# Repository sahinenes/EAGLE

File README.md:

## EAGLE 
# EAGLE YAZI KOMUTLARI 

group all;            # Her şeyi grupla
    
smash (C>0 0);       # Gruptaki her şeyi parçala
    
display none tNames bNames tval bval; #İSTEĞE BAĞLI: değişiklikleri sınırla
     isimler ve değerler
    
group all;             # Parçalanmış metinler dahil her şeyi gruplayın.
    
change font vector (C>0 0); # Yazı tipini vektör yazı tipine değiştirin
    
change size 50mil (C>0 0); # Yazı tipi boyutunu değiştirin
    
change ratio 15 (C>0 0); # Genişlik: yükseklik oranını değiştirin

display last; #Son halini göster

# LEZZETLİ ROBOT TARİFLERİ EAGLE BAŞLANGIÇ YAYINLARI

* https://www.youtube.com/watch?v=clBWAKnVNWI  # Sıfırdan EAGLE ile PCB tasarım yayınları başlıyor - ( Bölüm 0 )
* https://www.youtube.com/watch?v=m92im1b6kVI  # Eagle Ne ile Başlayıp, Sıfırdan Kart Çizip, Üretime Göndereceğiz! ( PART 1 / 2)
* https://www.youtube.com/watch?v=JgwcVjCoXeo  # Eagle Ne ile Başlayıp, Sıfırdan Kart Çizip, Üretime Göndereceğiz! ( PART 2 / 2)

# KAYNAKLAR 
* https://www.arduino.cc/en/uploads/Main/arduino_mini_schematic05.pdf # Arduino Mini Şematik 
* https://store.arduino.cc/usa/arduino-mini-05 # Arduino Mini EAGLE dosyaları bu linkten indirilebilir.

* https://www.researchgate.net/figure/L298N-Motor-Drive-Schematic_fig2_275414953 # L298N Şematik
* http://pdf.datasheetcatalog.com/datasheet/SGSThomsonMicroelectronics/mXxwur.pdf # L298N DataSheet
* https://www.ti.com/lit/ds/symlink/l293.pdf # L293D DataSheet

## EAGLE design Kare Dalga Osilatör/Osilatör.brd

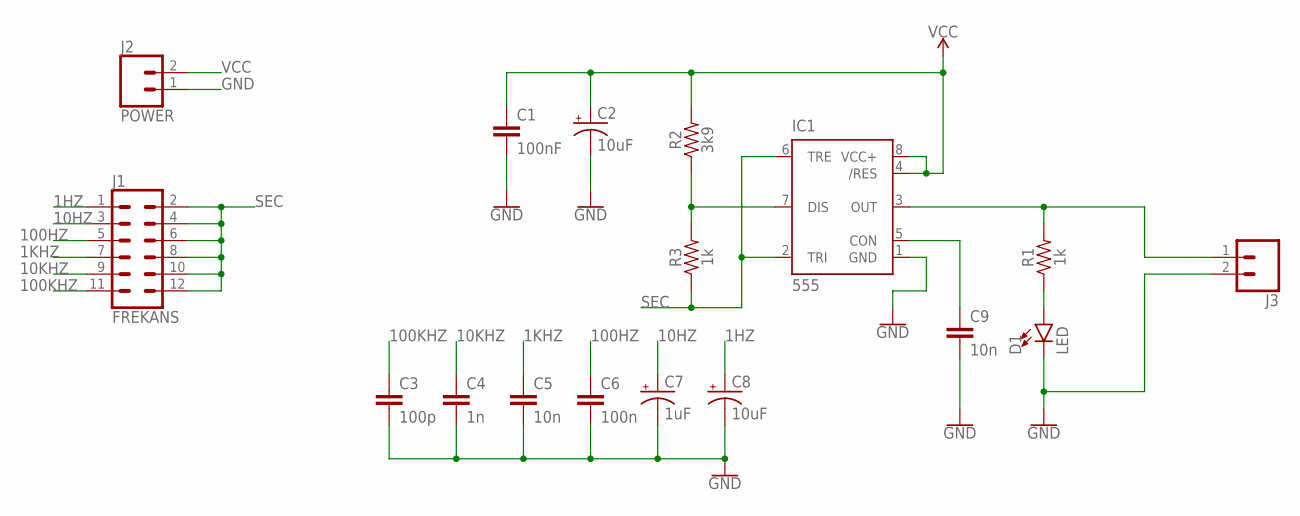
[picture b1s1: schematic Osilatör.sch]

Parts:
C1: 100nF; C2.5-3
C2, C8: 10uF; CPOL-RADIAL-2.5MM-6.5MM
C3: 100p; C2.5-3
C4: 1n; C2.5-3
C5, C9: 10n; C2.5-3
C6: 100n; C2.5-3
C7: 1uF; CPOL-RADIAL-2.5MM-6.5MM
D1: LED; LED_3MM-NS
IC1: 555; DIP08-KIT
J1: FREKANS; 2X6
J2: POWER; 1X02
J3: CONN_02; 1X02
R1, R3: 1k; AXIAL-0.3
R2: 3k9; AXIAL-0.3

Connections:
1HZ: C8.1 (+), J1.1
1KHZ: C5.1, J1.7
10HZ: C7.1 (+), J1.3
10KHZ: C4.1, J1.9
100HZ: C6.1, J1.5
100KHZ: C3.1, J1.11
GND: C1.2, C2.2 (-), C3.2, C4.2, C5.2, C6.2, C7.2 (-), C8.2 (-), C9.2, D1.K (C), IC1.1 (GND), J2.1, J3.2
unnamed: IC1.3 (OUT), J3.1, R1.P$2 (2)
unnamed: D1.A, R1.P$1 (1)
unnamed: C9.1, IC1.5 (CON)
unnamed: IC1.7 (DIS), R2.P$1 (1), R3.P$2 (2)
SEC: IC1.2 (TRI), IC1.6 (TRE), J1.2, J1.4, J1.6, J1.8, J1.10, J1.12, R3.P$1 (1)
VCC: C1.1, C2.1 (+), IC1.4 (/RES), IC1.8 (VCC+), J2.2, R2.P$2 (2)

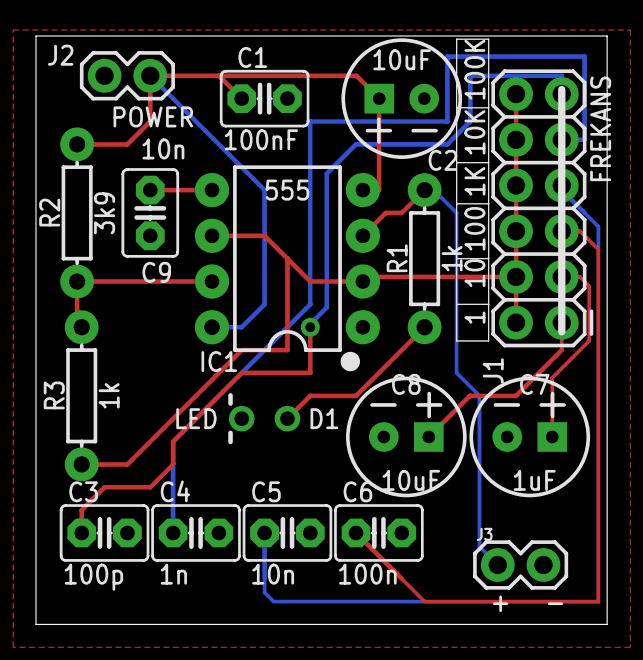
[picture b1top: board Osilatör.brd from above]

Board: 2 copper layers, 31.7 x 32.7 mm, 17 parts (0 on the bottom side), 13 nets.

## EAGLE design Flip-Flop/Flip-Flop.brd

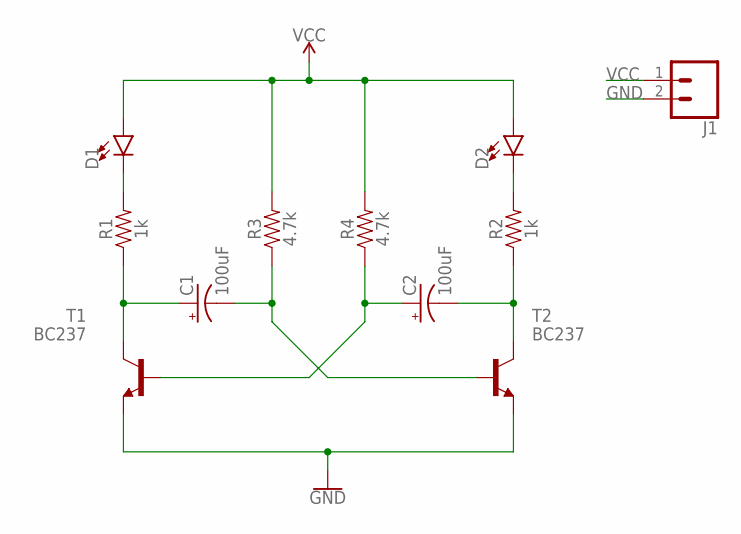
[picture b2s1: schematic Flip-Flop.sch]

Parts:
C1, C2: 100uF; CPOL-RADIAL-2.5MM-6.5MM
D1, D2: LED-3MM-NO_SILK; LED_3MM-NS
J1: CONN_02; 1X02
R1, R2: 1k; AXIAL-0.3
R3, R4: 4.7k; AXIAL-0.3
T1, T2: BC237; TO92

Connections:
GND: J1.2, T1.1 (E), T2.1 (E)
unnamed: D1.K (C), R1.P$2 (2)
unnamed: C1.1 (+), R1.P$1 (1), T1.3 (C)
unnamed: D2.K (C), R2.P$2 (2)
unnamed: C1.2 (-), R3.P$1 (1), T2.2 (B)
unnamed: C2.1 (+), R4.P$1 (1), T1.2 (B)
unnamed: C2.2 (-), R2.P$1 (1), T2.3 (C)
VCC: D1.A, D2.A, J1.1, R3.P$2 (2), R4.P$2 (2)

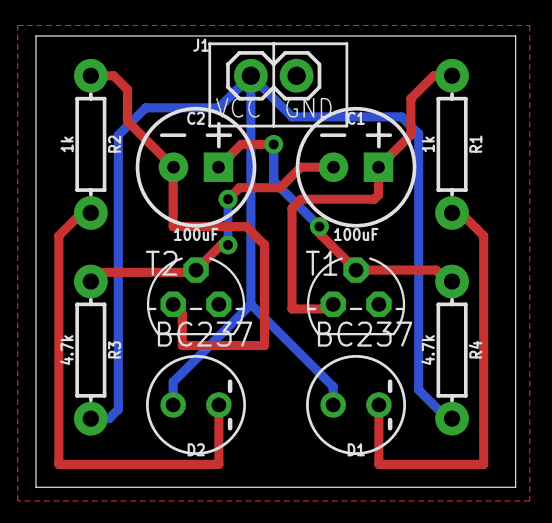
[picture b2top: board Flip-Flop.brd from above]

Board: 2 copper layers, 26.6 x 25.1 mm, 11 parts (0 on the bottom side), 8 nets.

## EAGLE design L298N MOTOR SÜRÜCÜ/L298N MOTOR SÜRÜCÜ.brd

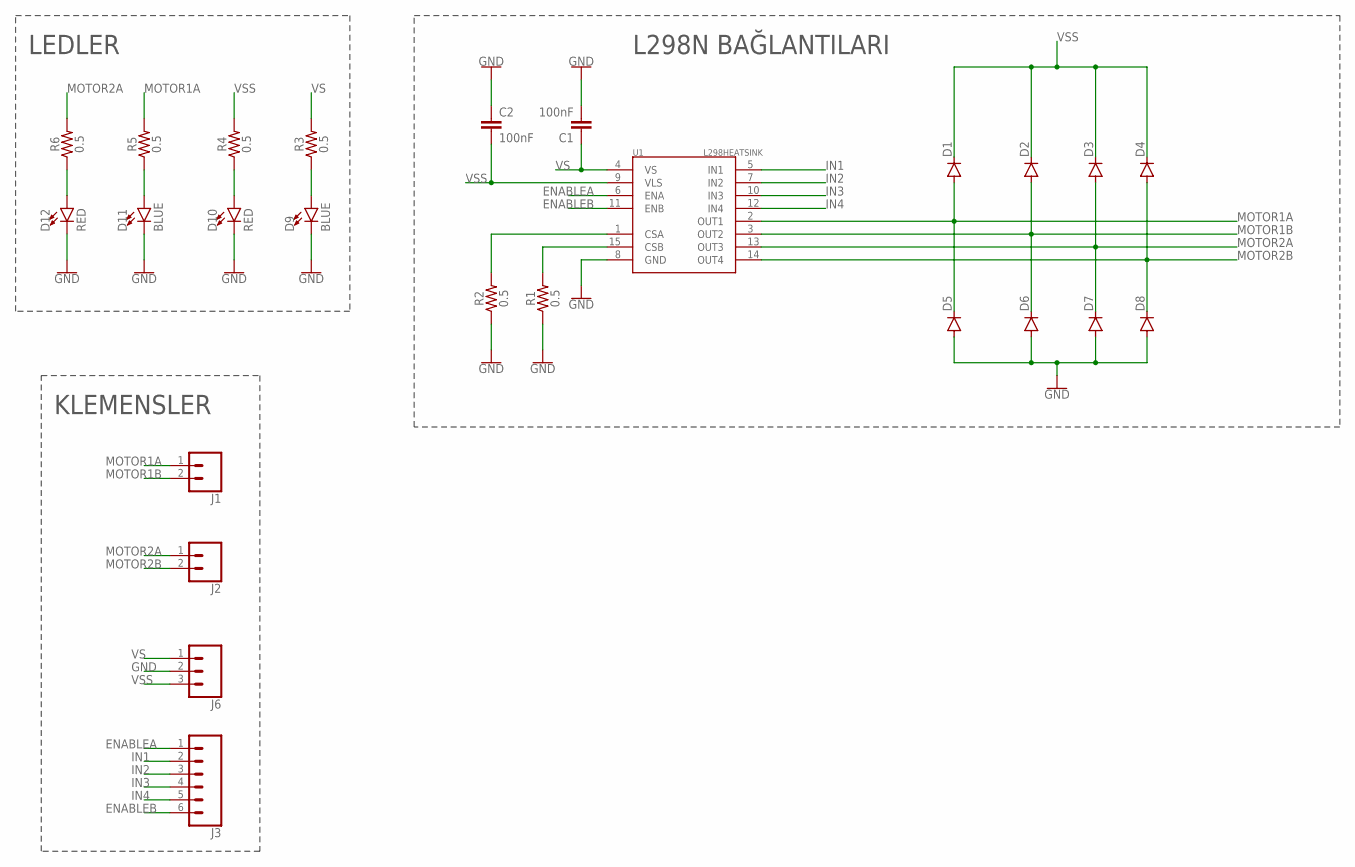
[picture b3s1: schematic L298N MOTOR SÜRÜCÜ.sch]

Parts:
C1, C2: 100nF; 0603
D1, D2, D3, D4, D5, D6, D7, D8: CGRM4007-G; SOD-123_MINI-SMA
D9, D11: BLUE; LED-0603
D10, D12: RED; LED-0603
J1, J2: CONN_02; 1X02
J3: CONN_06SILK_FEMALE_PTH; 1X06
J6: CONN_03; 1X03
R1, R2, R3, R4, R5, R6: 0.5; 0603
U1: L298HEATSINK; MULTIWATT15_6400BGHEATSINK

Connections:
ENABLEA: J3.1, U1.6 (ENA)
ENABLEB: J3.6, U1.11 (ENB)
GND: C1.2, C2.1, D5.A, D6.A, D7.A, D8.A, D9.C, D10.C, D11.C, D12.C, J6.2, R1.1, R2.1, U1.8 (GND)
IN1: J3.2, U1.5 (IN1)
IN2: J3.3, U1.7 (IN2)
IN3: J3.4, U1.10 (IN3)
IN4: J3.5, U1.12 (IN4)
MOTOR1A: D1.A, D5.C, J1.1, R5.2, U1.2 (OUT1)
MOTOR1B: D2.A, D6.C, J1.2, U1.3 (OUT2)
MOTOR2A: D3.A, D7.C, J2.1, R6.2, U1.13 (OUT3)
MOTOR2B: D4.A, D8.C, J2.2, U1.14 (OUT4)
unnamed: R1.2, U1.15 (CSB)
unnamed: R2.2, U1.1 (CSA)
unnamed: D10.A, R4.1
unnamed: D9.A, R3.1
unnamed: D12.A, R6.1
unnamed: D11.A, R5.1
VS: C1.1, J6.1, R3.2, U1.4 (VS)
VSS: C2.2, D1.C, D2.C, D3.C, D4.C, J6.3, R4.2, U1.9 (VLS)

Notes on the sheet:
KLEMENSLER
LEDLER
L298N BAĞLANTILARI

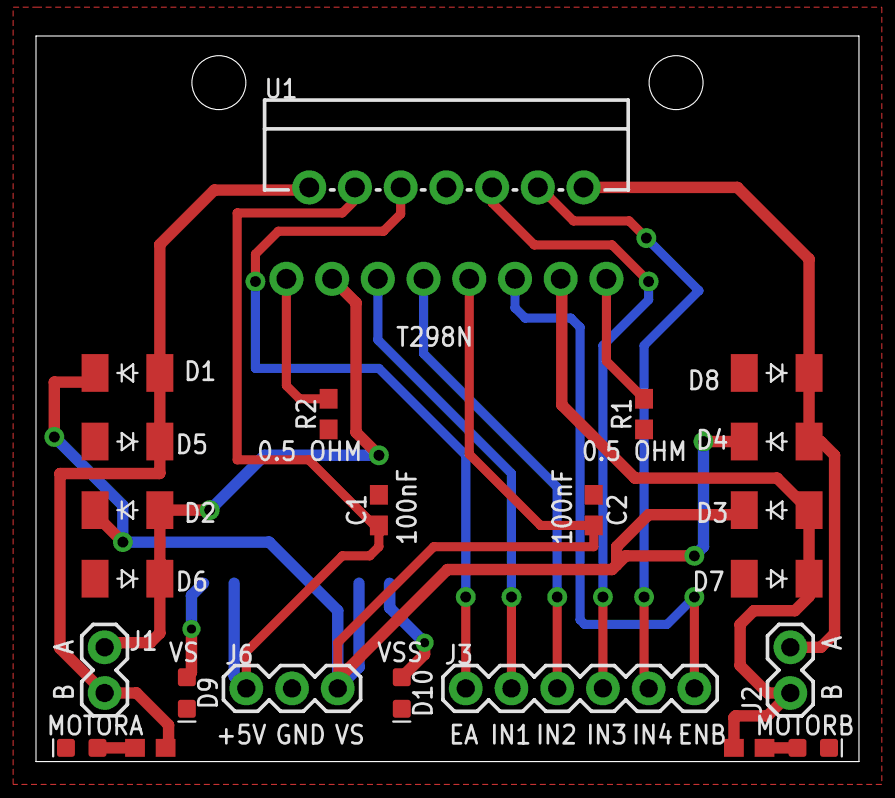
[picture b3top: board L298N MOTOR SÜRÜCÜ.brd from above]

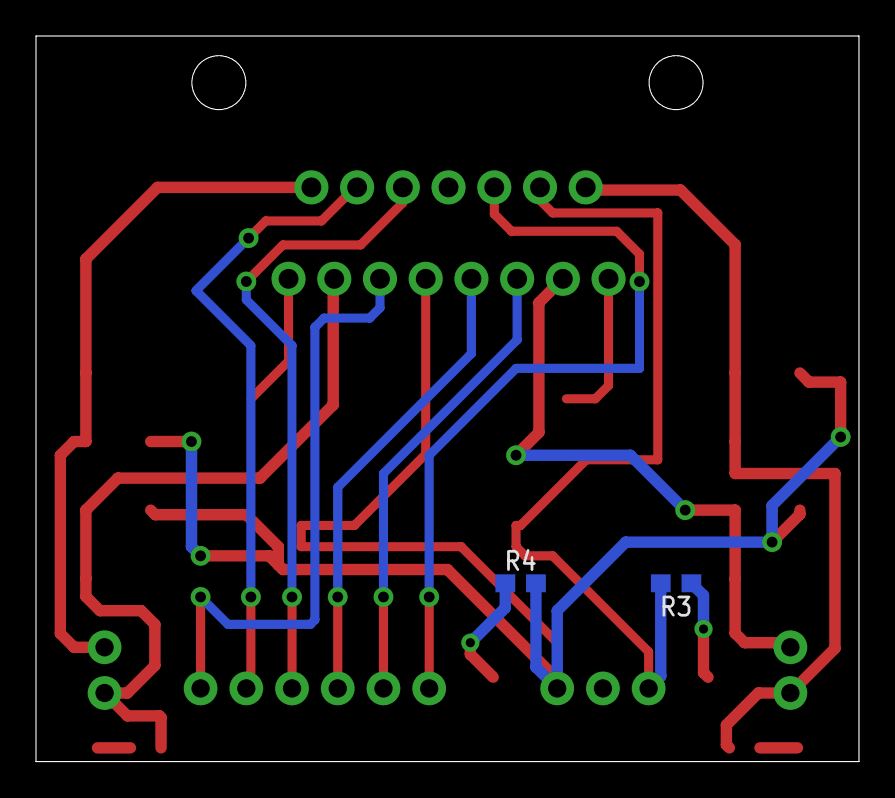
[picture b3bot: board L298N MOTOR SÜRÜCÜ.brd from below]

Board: 2 copper layers, 45.7 x 40.3 mm, 25 parts (2 on the bottom side), 19 nets.

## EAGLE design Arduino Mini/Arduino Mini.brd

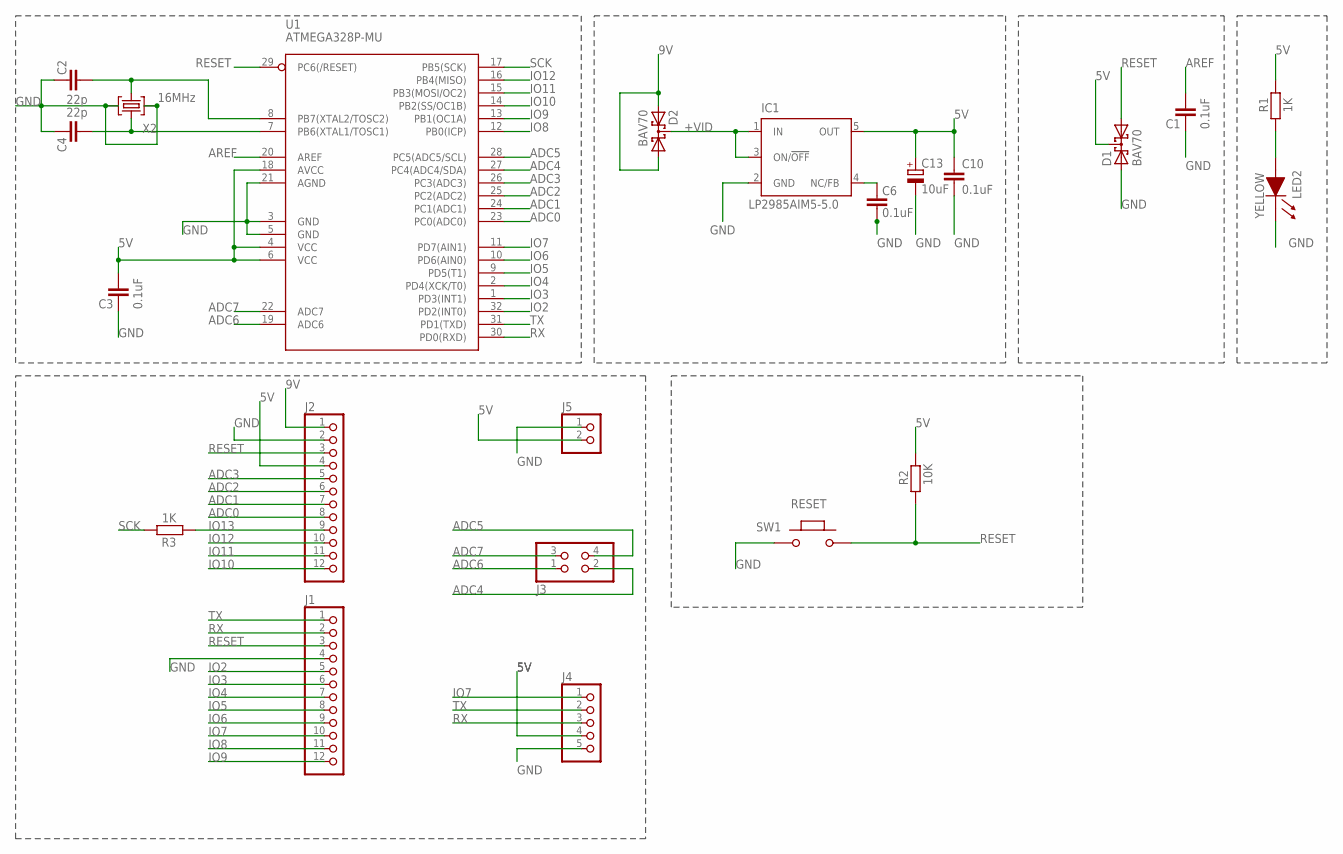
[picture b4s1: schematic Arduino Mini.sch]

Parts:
C1, C3, C6, C10: 0.1uF; C0603-ROUND
C2, C4: 22p; C0603-ROUND
C13: 10uF; SMC_B
D1, D2: BAV70; SOT23
IC1: LP2985AIM5-5.0; SOT23-DBV
J1, J2: PINHD-1X12; 1X12
J3: PINHD-2X2; 2X02
J4: PINHD-1X5; 1X5
J5: PINHD-1X2; 1X2
LED2: YELLOW; SMD_LED0805
R1, R3: 1K; R0603-ROUND
R2: 10K; R0603-ROUND
SW1: RESET; SMD_157SW
U1: ATMEGA328P-MU; MLF32-M1-A
X2: 16MHz; CRYSTAL-3.2-2.5

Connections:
5V: C3.1, C10.1, C13.+, D1.3 (C), IC1.5 (OUT), J2.4, J4.4, J5.2, R1.2, R2.2, U1.4 (VCC), U1.6 (VCC), U1.18 (AVCC)
9V: D2.1 (A1), D2.2 (A2), J2.1
+VID: D2.3 (C), IC1.1 (IN), IC1.3 (ON/!OFF)
ADC0: J2.8, U1.23 (PC0(ADC0))
ADC1: J2.7, U1.24 (PC1(ADC1))
ADC2: J2.6, U1.25 (PC2(ADC2))
ADC3: J2.5, U1.26 (PC3(ADC3))
ADC4: J3.2, U1.27 (PC4(ADC4/SDA))
ADC5: J3.4, U1.28 (PC5(ADC5/SCL))
ADC6: J3.1, U1.19 (ADC6)
ADC7: J3.3, U1.22 (ADC7)
AREF: C1.1, U1.20 (AREF)
GND: C1.2, C2.2, C3.2, C4.2, C6.1, C10.2, C13.-, D1.1 (A1), IC1.2 (GND), J1.4, J2.2, J4.5, J5.1, LED2.1 (CA), SW1.1, U1.3 (GND), U1.5 (GND), U1.21 (AGND), X2.2 (GND), X2.4 (GND)
IO2: J1.5, U1.32 (PD2(INT0))
IO3: J1.6, U1.1 (PD3(INT1))
IO4: J1.7, U1.2 (PD4(XCK/T0))
IO5: J1.8, U1.9 (PD5(T1))
IO6: J1.9, U1.10 (PD6(AIN0))
IO7: J1.10, J4.1, U1.11 (PD7(AIN1))
IO8: J1.11, U1.12 (PB0(ICP))
IO9: J1.12, U1.13 (PB1(OC1A))
IO10: J2.12, U1.14 (PB2(SS/OC1B))
IO11: J2.11, U1.15 (PB3(MOSI/OC2))
IO12: J2.10, U1.16 (PB4(MISO))
IO13: J2.9, R3.1
unnamed: C2.1, U1.8 (PB7(XTAL2/TOSC2)), X2.3 (C2)
unnamed: C6.2, IC1.4 (NC/FB)
unnamed: C4.1, U1.7 (PB6(XTAL1/TOSC1)), X2.1 (C1)
RESET: D1.2 (A2), J1.3, J2.3, R2.1, SW1.2, U1.29 (PC6(/RESET))
RESET1: LED2.2 (AN), R1.1
RX: J1.2, J4.3, U1.30 (PD0(RXD))
SCK: R3.2, U1.17 (PB5(SCK))
TX: J1.1, J4.2, U1.31 (PD1(TXD))

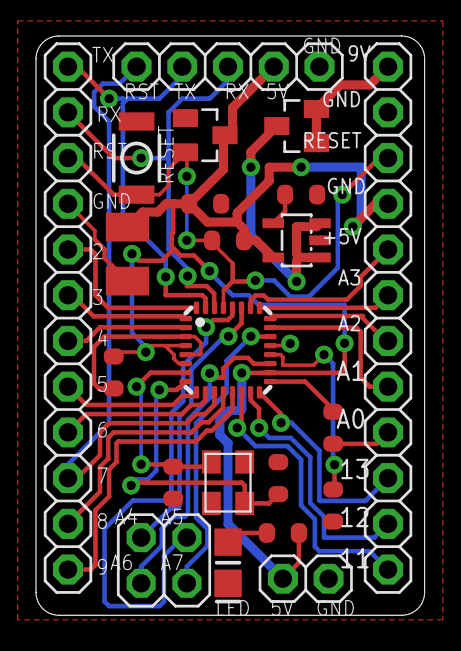
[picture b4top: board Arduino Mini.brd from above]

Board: 2 copper layers, 21.6 x 32.2 mm, 22 parts (0 on the bottom side), 33 nets.

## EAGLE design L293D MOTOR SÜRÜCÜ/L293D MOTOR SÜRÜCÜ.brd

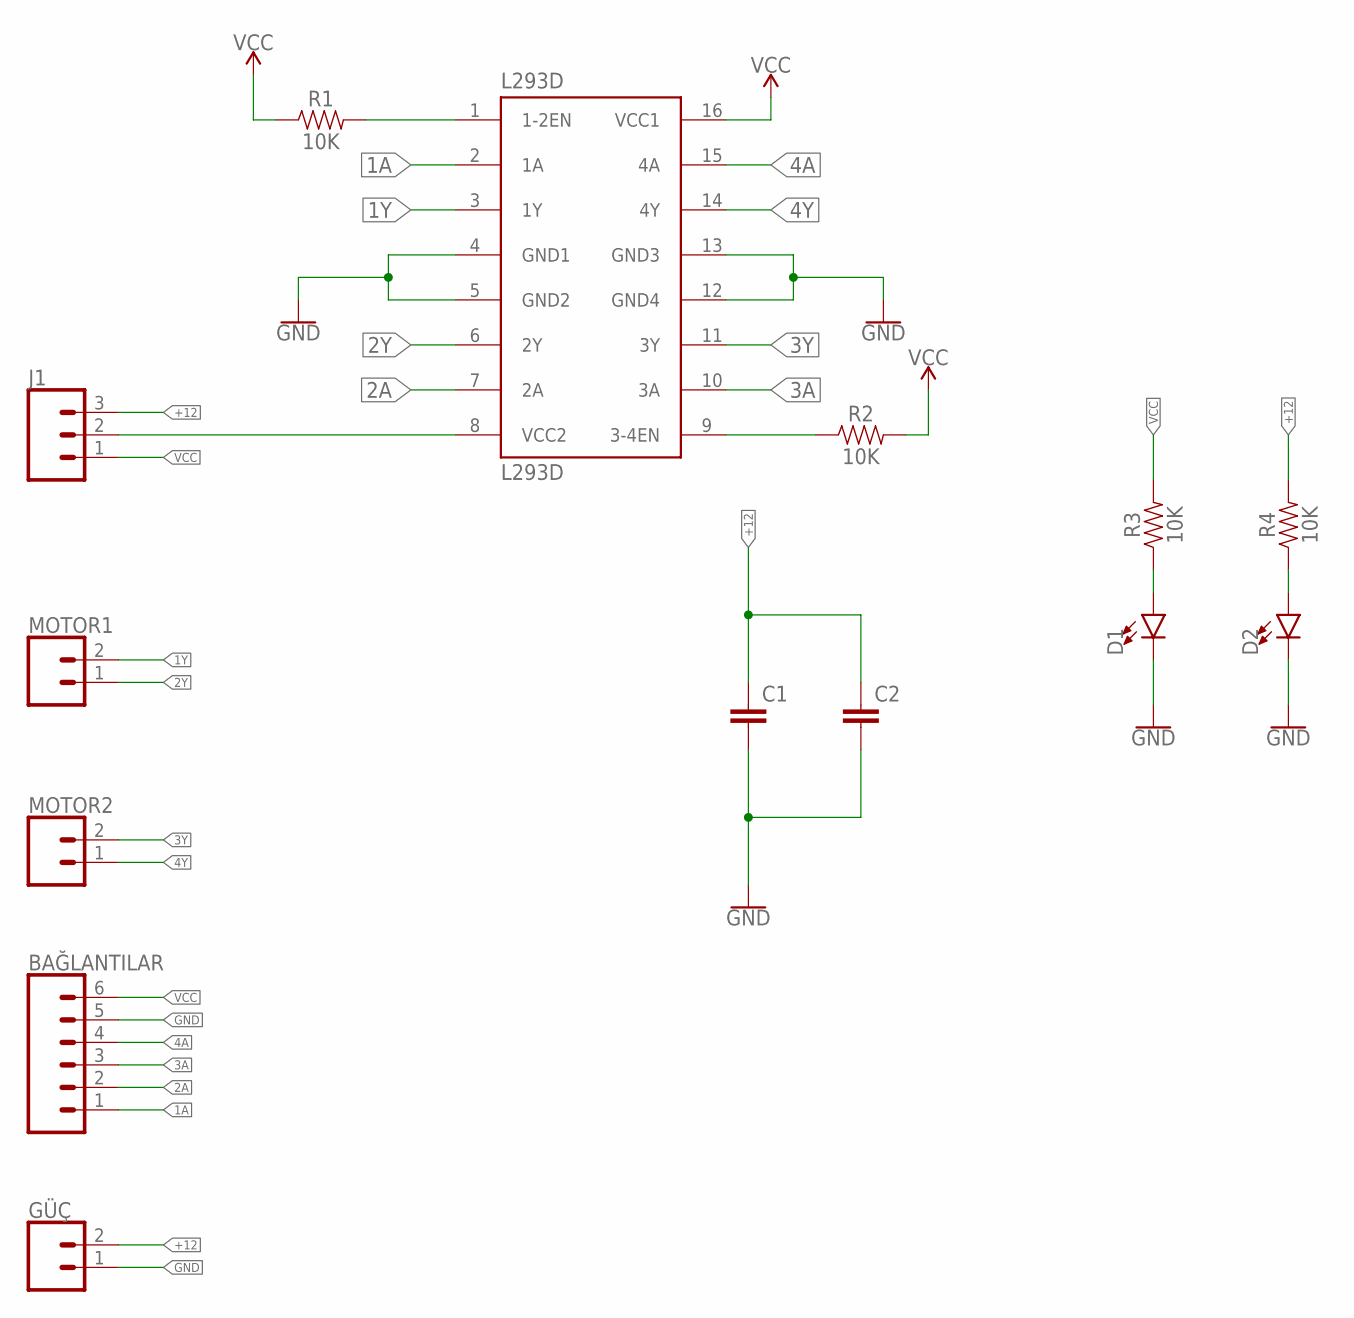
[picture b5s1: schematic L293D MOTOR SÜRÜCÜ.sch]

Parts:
BAĞLANTILAR: CONN_06LOCK; 1X06_LOCK
C1, C2: C2,5-3; C2.5-3
D1, D2: LED-3MM-NO_SILK; LED_3MM-NS
GÜÇ: CONN_02; 1X02
J1: CONN_03; 1X03
L293D: L293D; DIL16
MOTOR1, MOTOR2: CONN_02; 1X02
R1, R2, R3, R4: 10K; AXIAL-0.3

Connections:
1A: BAĞLANTILAR.1, L293D.2 (1A)
1Y: L293D.3 (1Y), MOTOR1.2
2A: BAĞLANTILAR.2, L293D.7 (2A)
2Y: L293D.6 (2Y), MOTOR1.1
3A: BAĞLANTILAR.3, L293D.10 (3A)
3Y: L293D.11 (3Y), MOTOR2.2
4A: BAĞLANTILAR.4, L293D.15 (4A)
4Y: L293D.14 (4Y), MOTOR2.1
+12: C1.1, C2.1, GÜÇ.2, J1.3, R4.P$2 (2)
GND: BAĞLANTILAR.5, C1.2, C2.2, D1.K (C), D2.K (C), GÜÇ.1, L293D.4 (GND1), L293D.5 (GND2), L293D.12 (GND4), L293D.13 (GND3)
unnamed: J1.2, L293D.8 (VCC2)
unnamed: D2.A, R4.P$1 (1)
unnamed: L293D.1 (1-2EN), R1.P$2 (2)
unnamed: L293D.9 (3-4EN), R2.P$1 (1)
unnamed: D1.A, R3.P$1 (1)
VCC: BAĞLANTILAR.6, J1.1, L293D.16 (VCC1), R1.P$1 (1), R2.P$2 (2), R3.P$2 (2)

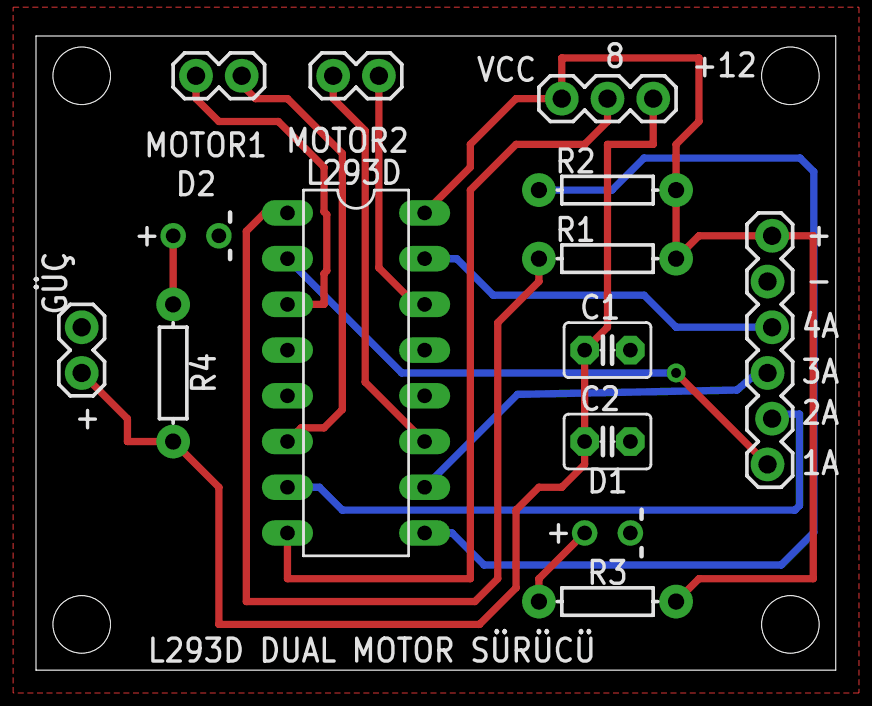
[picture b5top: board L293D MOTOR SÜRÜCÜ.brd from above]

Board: 2 copper layers, 44.4 x 35.2 mm, 14 parts (0 on the bottom side), 16 nets.

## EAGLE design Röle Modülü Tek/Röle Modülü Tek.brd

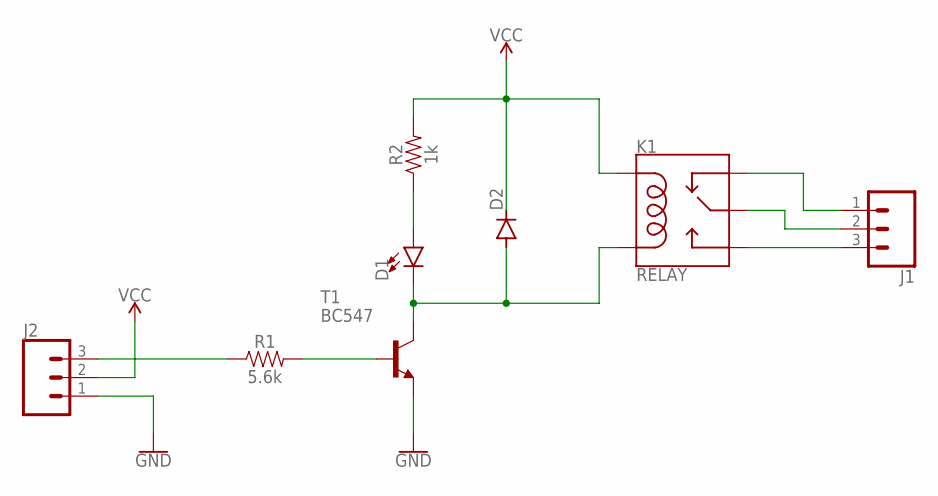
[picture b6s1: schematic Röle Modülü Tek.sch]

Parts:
D1: LED3MM; LED_3MM
D2: DIODE-DO07; DO07
J1, J2: CONN_03; 1X03
K1: RELAY; RELAY-JZC
R1: 5.6k; AXIAL-0.3
R2: 1k; AXIAL-0.3
T1: BC547; TO92

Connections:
GND: J2.1, T1.1 (E)
unnamed: R1.P$2 (2), T1.2 (B)
unnamed: D1.K (C), D2.A, K1.1 (COIL2), T1.3 (C)
unnamed: D1.A, R2.P$1 (1)
unnamed: J2.3, R1.P$1 (1)
unnamed: J1.1, K1.2 (NC)
unnamed: J1.2, K1.4 (MAIN)
unnamed: J1.3, K1.3 (NO)
VCC: D2.C, J2.2, K1.5 (COIL1), R2.P$2 (2)

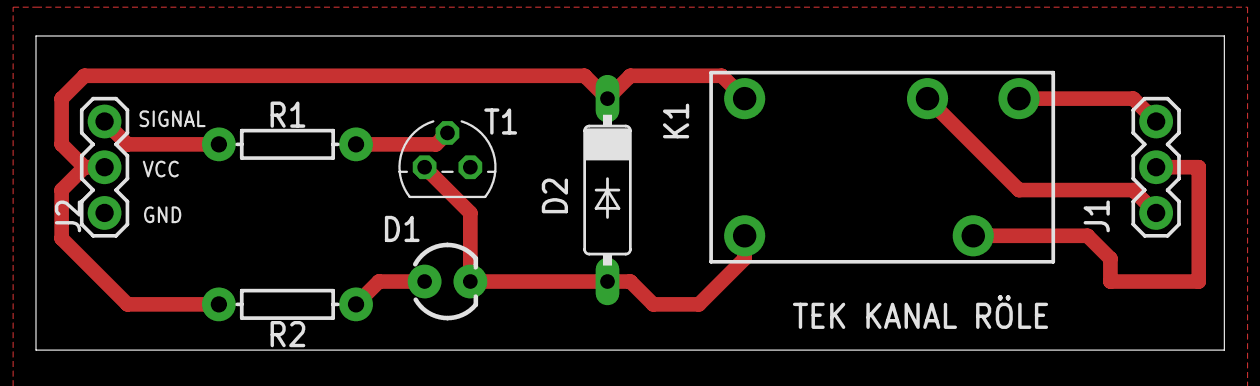
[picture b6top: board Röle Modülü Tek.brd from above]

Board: 2 copper layers, 66.0 x 17.4 mm, 8 parts (0 on the bottom side), 9 nets.

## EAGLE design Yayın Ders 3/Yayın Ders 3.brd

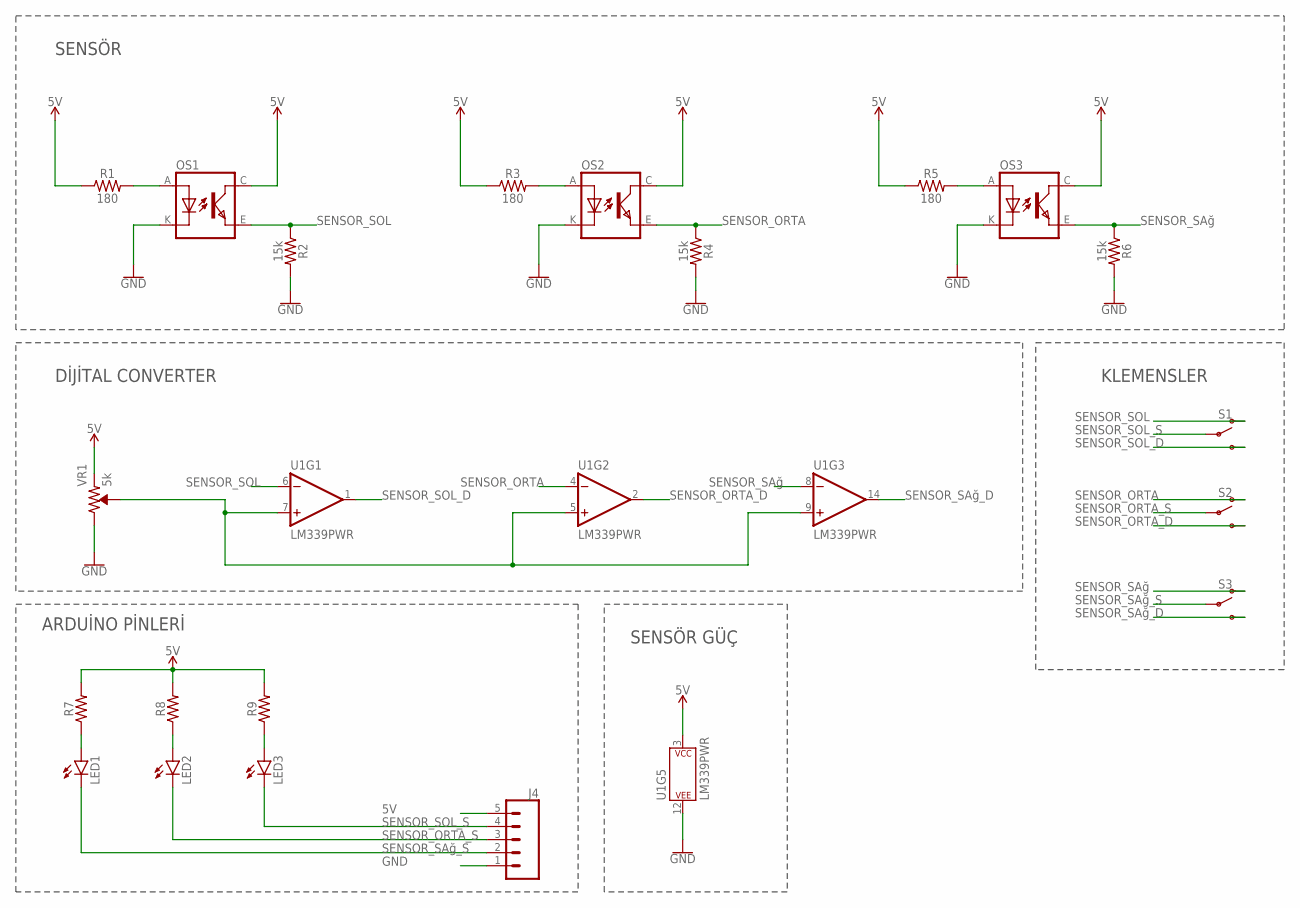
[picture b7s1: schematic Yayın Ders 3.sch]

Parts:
J4: CONN_05; 1X05
LED1, LED2, LED3: LEDCHIP-LED0805; CHIP-LED0805
OS1, OS2, OS3: TCRT5000
R1, R3, R5: 180; 0805
R2, R4, R6: 15k; 0805
R7, R8, R9: 0805
S1, S2, S3: SWITCH-SPDT-SMD-RIGHT-ANGLE; SWITCH_SPST_SMD_A
U1: LM339PWR; TSSOP-14
VR1: 5k; TRIMPOT-SMD-5MM

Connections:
5V: J4.5, OS1.C (COLLECTOR), OS2.C (COLLECTOR), OS3.C (COLLECTOR), R1.1, R3.1, R5.1, R7.2, R8.2, R9.2, U1.3 (P$V+), VR1.A (CCW)
GND: J4.1, OS1.K (CATHODE), OS2.K (CATHODE), OS3.K (CATHODE), R2.2, R4.2, R6.2, U1.12 (P$V-), VR1.C (CW)
unnamed: OS1.A (ANODE), R1.2
unnamed: LED1.A, R7.1
unnamed: OS2.A (ANODE), R3.2
unnamed: LED2.A, R8.1
unnamed: OS3.A (ANODE), R5.2
unnamed: LED3.A, R9.1
unnamed: U1.5 (+IN), U1.7 (+IN), U1.9 (+IN), VR1.B (WIPER)
SENSOR_ORTA: OS2.E (EMITTER), R4.1, S2.1 (O), U1.4 (-IN)
SENSOR_ORTA_D: S2.3 (S), U1.2 (OUT)
SENSOR_ORTA_S: J4.3, LED2.C, S2.2
SENSOR_SAğ: OS3.E (EMITTER), R6.1, S3.1 (O), U1.8 (-IN)
SENSOR_SAğ_D: S3.3 (S), U1.14 (OUT)
SENSOR_SAğ_S: J4.2, LED1.C, S3.2
SENSOR_SOL: OS1.E (EMITTER), R2.1, S1.1 (O), U1.6 (-IN)
SENSOR_SOL_D: S1.3 (S), U1.1 (OUT)
SENSOR_SOL_S: J4.4, LED3.C, S1.2

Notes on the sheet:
SENSÖR
SENSÖR GÜÇ
DİJİTAL CONVERTER
ARDUİNO PİNLERİ
KLEMENSLER

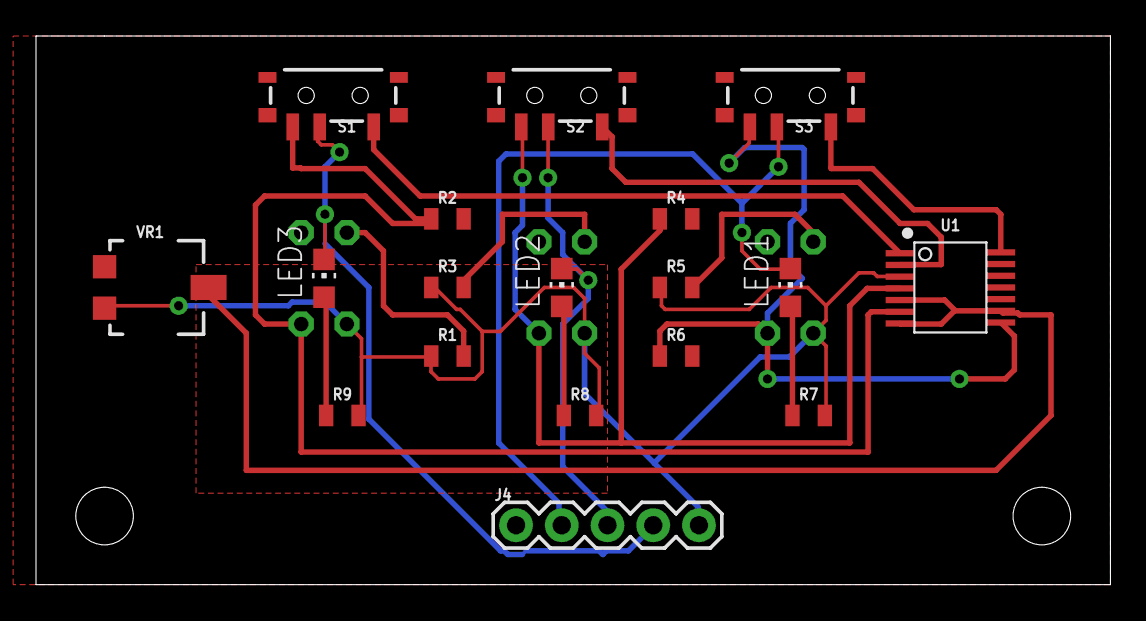
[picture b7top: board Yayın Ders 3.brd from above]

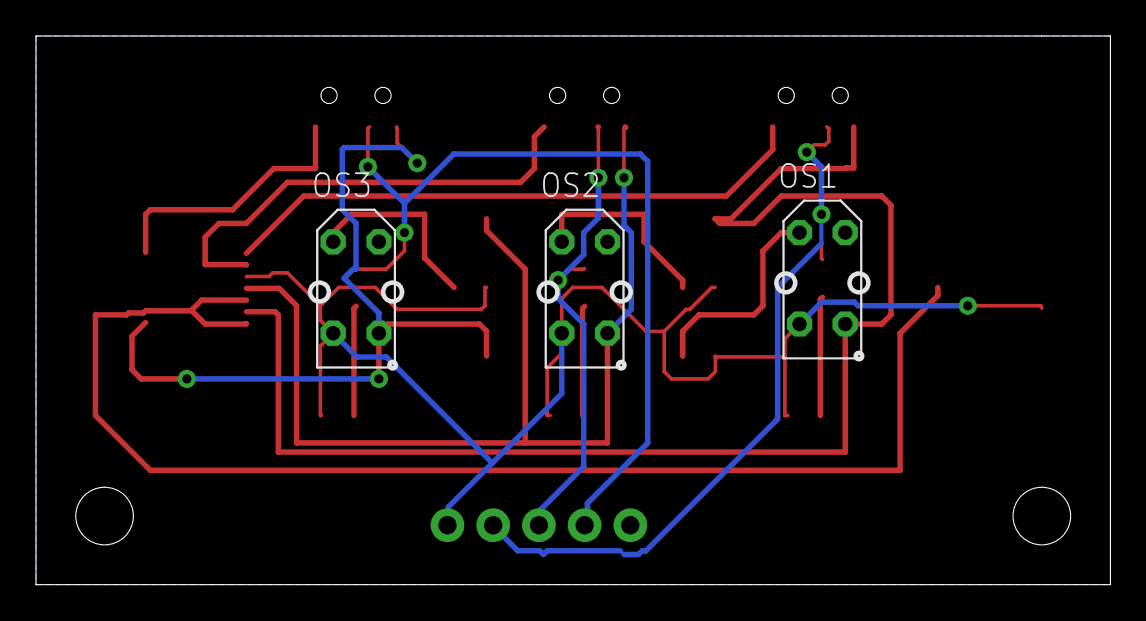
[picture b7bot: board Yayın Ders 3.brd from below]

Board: 2 copper layers, 59.7 x 30.5 mm, 21 parts (3 on the bottom side), 18 nets.

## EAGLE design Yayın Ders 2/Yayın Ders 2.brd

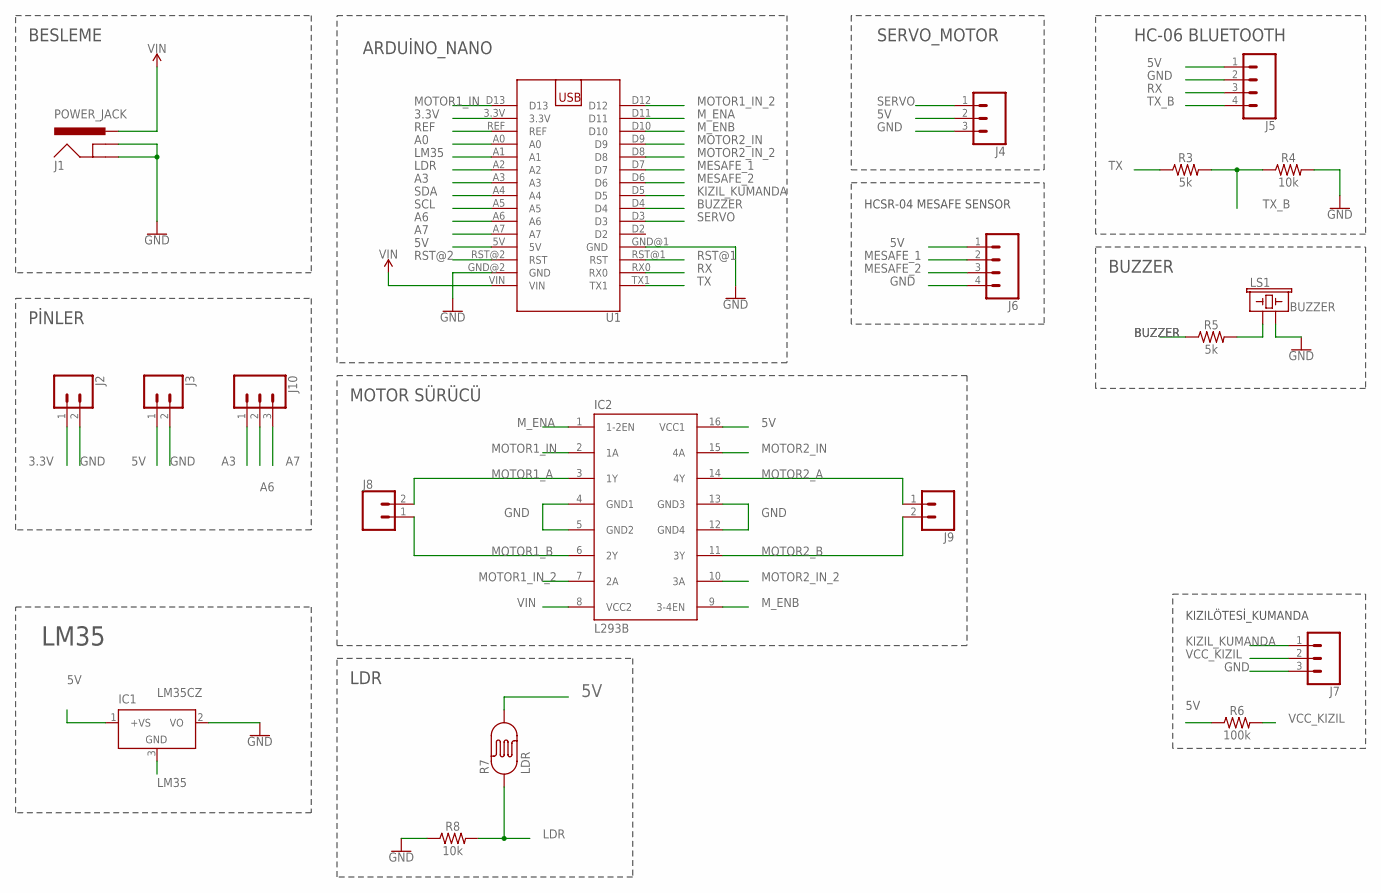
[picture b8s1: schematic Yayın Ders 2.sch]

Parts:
IC1: LM35CZ; TO92
IC2: L293B; DIL16
J1: POWER_JACK; POWER_JACK_PTH
J2, J3, J8, J9: CONN_02; 1X02
J4, J7, J10: CONN_03; 1X03
J5, J6: CONN_04; 1X04
LS1: BUZZER; BUZZER-12MM
R3, R5: 5k; AXIAL-0.3
R4, R8: 10k; AXIAL-0.3
R6: 100k; AXIAL-0.3
R7: LDR; PHOTOCELL
U1: ARDUINO_NANO

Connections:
3.3V: J2.1, U1.3.3V
5V: IC1.1 (+VS), IC2.16 (VCC1), J3.1, J4.2, J5.1, J6.1, R6.P$1 (1), R7.2, U1.5V
A0: U1.A0
A3: J10.1, U1.A3
A6: J10.2, U1.A6
A7: J10.3, U1.A7
BUZZER: R5.P$1 (1), U1.D4
GND: IC1.2 (VO), IC2.4 (GND1), IC2.5 (GND2), IC2.12 (GND4), IC2.13 (GND3), J1.GND, J1.GNDBREAK, J2.2, J3.2, J4.3, J5.2, J6.4, J7.3, LS1.- (2), R4.P$2 (2), R8.P$1 (1), U1.GND@1 (GND), U1.GND@2 (GND)
KIZIL_KUMANDA: J7.1, U1.D5
LDR: R7.1, R8.P$2 (2), U1.A2
LM35: IC1.3 (GND), U1.A1
MESAFE_1: J6.2, U1.D7
MESAFE_2: J6.3, U1.D6
MOTOR1_A: IC2.3 (1Y), J8.2
MOTOR1_B: IC2.6 (2Y), J8.1
MOTOR1_IN: IC2.2 (1A), U1.D13
MOTOR1_IN_2: IC2.7 (2A), U1.D12
MOTOR2_A: IC2.14 (4Y), J9.1
MOTOR2_B: IC2.11 (3Y), J9.2
MOTOR2_IN: IC2.15 (4A), U1.D9
MOTOR2_IN_2: IC2.10 (3A), U1.D8
M_ENA: IC2.1 (1-2EN), U1.D11
M_ENB: IC2.9 (3-4EN), U1.D10
unnamed: LS1.+ (1), R5.P$2 (2)
REF: U1.REF
RST@1: U1.RST@1 (RST)
RST@2: U1.RST@2 (RST)
RX: J5.3, U1.RX0
SCL: U1.A5
SDA: U1.A4
SERVO: J4.1, U1.D3
TX: R3.P$1 (1), U1.TX1
TX_B: J5.4, R3.P$2 (2), R4.P$1 (1)
VCC_KIZIL: J7.2, R6.P$2 (2)
VIN: IC2.8 (VCC2), J1.PWR, U1.VIN

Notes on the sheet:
BESLEME
ARDUİNO_NANO
SERVO_MOTOR
HC-06 BLUETOOTH
HCSR-04 MESAFE SENSOR
BUZZER
LM35
KIZILÖTESİ_KUMANDA
LDR
MOTOR SÜRÜCÜ
PİNLER

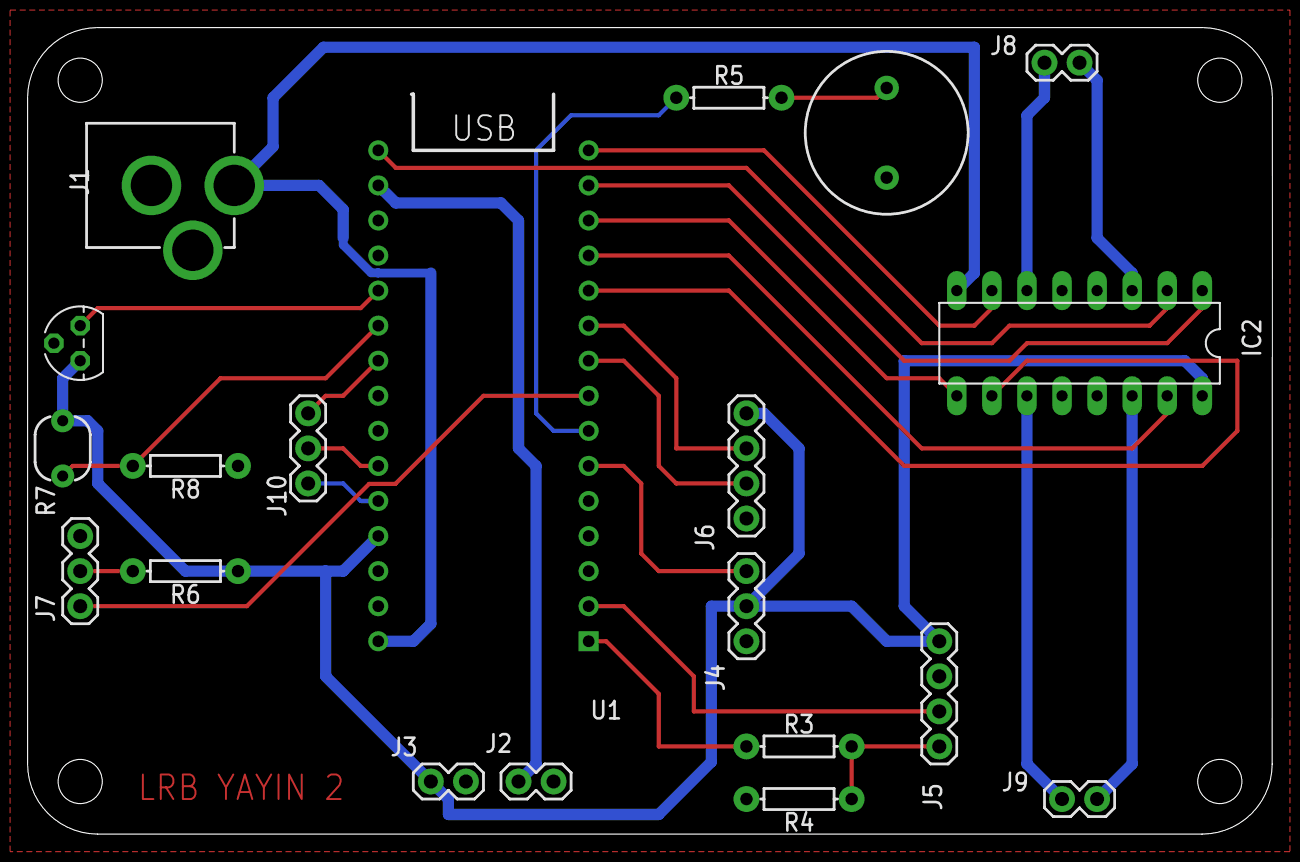
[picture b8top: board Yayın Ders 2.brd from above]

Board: 2 copper layers, 90.2 x 58.4 mm, 20 parts (0 on the bottom side), 29 nets.

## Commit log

2020-11-13 Oluşturuldu
2020-11-13 Lezzetli Robot Tarifleri Yayın 1
2020-11-13 Lezzetli Robot Tarifleri Yayın 2
2020-11-13 Lezzetli Robot Tarifleri Yayın 3
2020-11-13 Röle Modülleri
2020-11-13 Motor Sürücü
2020-11-13 Arduino Mini Çizimi
2020-11-15 L298N ÇİFT MOTOR SÜRÜCÜ
2020-11-15 EAGLE Notlarım
2020-11-18 Flip-Flop Devresi
2020-11-18 Kare Dalga Osilatör
2020-12-08 deneme branch i
2020-12-12 README.md değişti
2020-12-12 deneme
2020-12-12 README.md
2020-12-12 Eagle Katmanlar

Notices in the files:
parts and their libraries:
SparkFun-Aesthetics: Licensing: Creative Commons ShareAlike 4.0 International - https://creativecommons.org/licenses/by-sa/4.0
